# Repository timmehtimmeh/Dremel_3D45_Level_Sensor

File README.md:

# Dremel_3D45_Level_Sensor
KiCAD project, schematic, and gerbers of a Printed Circuit Board (PCB) replacement for The Auto_LevelBoard PCB for the Dremel 3D45 (and possibly the Dremel 3D40)
  **NOTE** Using this PCB will likely void any warranty provided with the printer.  An entire replacement leveling arm assembly can be [purchased directly from 3PITech](https://3pitech.com/products/3d45-leveling-sensor)

# Getting the Gerbers
If you only want to have the PCBs manufactured, navigate to the [releases page](https://github.com/timmehtimmeh/Dremel_3D45_Level_Sensor/releases/) and download the zip file of the gerbers

# Cloning the repo
This repository references the KiCAD symbol and footprint libraries stored in [Tims-KiCad-Library](https://github.com/timmehtimmeh/Tims-KiCad-Library) to properly clone this repo please type the following into a git command window:

```git clone --recurse-submodules https://github.com/timmehtimmeh/Dremel_3D45_Level_Sensor.git```

# Parts required

The following parts are required to replace the PCB

| Part | Qty | Link | Notes|
|------|-----|------|------|
| PCB | 1 | I had the gerbers successfully manufactured at [JLCPCB](https://jlcpcb.com/) as well as [OSHPark*](https://oshpark.com/shared_projects/k3kUrSLB) | * **NOTE:** The original Dremel PCB is 1mm thick.  OshPark only makes standard thickness 1.6 mm boards, but the thicker 1.6mm board worked fine in the printer. JLCPCB has options for 1mm thick boards |
| Switch | 1 | The OEM seems to be a [Panasonic ESE-31R15T](https://www.digikey.com/en/products/detail/panasonic-electronic-components/ESE-31R15T/3163183) | An alternate can be the [TE Connectivity JJJHRGG200NOPMRTR](https://www.digikey.com/en/products/detail/te-connectivity-alcoswitch-switches/JJJHRGG200NOPMRTR/9452492), but in testing the Panasonic part was less prone to getting stuck in the housing |
| Jumper Wire | 2  | [Wire](https://www.amazon.com/dp/B089CWGQKW) |  The OEM is 26 AWG stranded wire, 90 mm, 1 red, one black Outer Diameter (O.D) 1mm. I used the 1.2 mm O.D. 28 AWG silicone coated wire linked, and it still fits inside the cable routing cutouts on the level arm. |
| 2 Position JST-PH 2mm Connector | 1 | [JST Kit](https://www.amazon.com/dp/B0F485CN38) | I used the kit linked, however you can also buy pre-assembled wires  |

Additionally Soldering equipment (iron, solder), and either Silicone glue, or Hot Glue are needed to complete the job.

# Assembly Instructions

Tools Needed
1.  2mm Hex bit or Hex wrench (Allen key)
2.  T10 Torx (star) screwdriver
3.  T7 Torx (star) screwdriver
4.  Replacement PCB

Once you have gathered the necessary components, assembly is relatively straightforward.
1. Place the switch onto the PCB such that the alignment holes in the bottom of the switch mate with the holes in the PCB
2. Ensure that the switch is centered and square to the board
3. Solder on one of the four pads of the switch.
4. Check Alignment of the switch.  If it's moved heat up the one pad and move the switch until it's square with the board and then let the solder cool
5. Solder the remaining three pads of the switch
6. (Optional) Solder the two jumper pads such that the jumpers make contact. This connects the switch housing to one leg of the switch.  If using the TE Connectivity switch there is no metal housing and this step can be skipped.  If using the Panasonic switch then the circuit will work with or without the jumpers connected together.
7. Strip approximately 2mm of insulation off of one end of each of a black and red wire.
8. Crimp JST-PH connectors onto each of the wires
9. Push the crimped end into a two position JST-PH connector (the red/black orientation doesn't matter, but I kept mine the same as the original board)
10. Cut the wires such that they're both equal in length, and the same length as the OEM wire (approximately 90mm)
11. Strip 2-3mm of insulation off the cut end of the wire
12. Solder the red wire onto the PCB where the silkscreen indicates the red wire should go
13. Solder the black wire onto the PCB where the silkscreen indicates the black wire should go
14. Place the board on something that will allow you to put some silicone or hot glue onto the wires & board
15. Put a blob of glue such that it covers the two soldered ends of the wire and travels a bit up the wire to provide some strain relief.  Be sure to not allow too much glue to blob on the back side of the PCB
16. Once the glue is set, follow Steps 1, 2, and 5 from [these instructions](https://cdn.shopify.com/s/files/1/0552/1797/9558/files/3d45-3d40-leveling-arm-replacement.pdf)
17. Unscrew the PCB from the leveling arm assembly on your printer, taking care to not lose the screw or washer that holds the PCB in place
18. Carefully pull the wires out of the plastic wire guide on the leveling arm assembly, and remove the old PCB from the assembly
19. Thread the JST-PH connector from the new PCB through the appropriate area in the 3D printer head assembly and attach it to the printer, re-attach the servo motor wire if it was disconnected
20. Place the PCB into the sensor arm such that the plastic locating pin holds the PCB in place.
21. Using the T7 torx screwdriver, attach PCB using the screw & washer that was taken out in Step 17.
22. Reassemble the Extruder by following Step 6 in [these instructions](https://cdn.shopify.com/s/files/1/0552/1797/9558/files/3d45-3d40-leveling-arm-replacement.pdf)
23. If necessary, calibrate the level arm up/down position by navigating to TOOLS>SETTINGS>SERVICE TOOLS>LEVELING SWITCH and set the level (Step 7 in the linked instructions)
24. Calibrate the nozzle gap by following [these instructions](https://www.dremel.com/binaries/content/assets/dremel/uk/digilab/how-to-self-repair/3d45/3d45-nozzle-gap-calibration.pdf)

**Notes** - After a few uses I found that the replacment switch was not rebounding as quickly as it should.  To fix this i used a little bit of nonconductive spray lubricant on the tip of the switch and moved the switch in and out a few times after which the switch rebounded much more quickly.

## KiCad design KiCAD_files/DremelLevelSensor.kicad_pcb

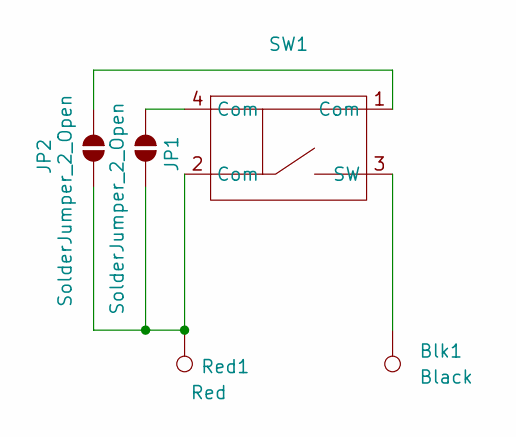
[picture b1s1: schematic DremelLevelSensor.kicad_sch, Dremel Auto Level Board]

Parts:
Blk1: Black; TestPoint_Pad_D1.5mm
JP1, JP2: SolderJumper_2_Open; SolderJumper-2_P1.3mm_Open_RoundedPad1.0x1.5mm
Red1: Red; TestPoint_Pad_D1.5mm
SW1: ESE31R11T

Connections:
GND: JP1.1 (A), JP2.1 (A), Red1.1, SW1.2 (Com)
unnamed: JP1.2 (B), SW1.4 (Com)
unnamed: JP2.2 (B), SW1.1 (Com)
unnamed: Blk1.1, SW1.3 (SW)

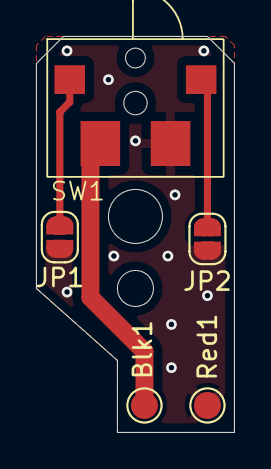
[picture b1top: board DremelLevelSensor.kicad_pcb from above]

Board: 2 copper layers, 11.0 x 22.0 mm, 5 parts (0 on the bottom side), 4 nets.

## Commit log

2026-02-08 Update README to include KiCAD project details
2026-02-08 Add KiCad files
2026-02-08 Add kicad gitignore file
2026-02-08 fix markdown table
2026-02-08 space between header and table
2026-02-08 Fix table
2026-02-08 fix links
2026-02-08 fix text in wire section
2026-02-08 Update OSHPark Link
2026-02-08 Add image, update README
2026-02-08 Update PCB and Schematic to remove unnecessary jumper that was added to try to get DKRed to work
2026-02-08 Move KiCAD Files folder, add pdf of schematic
2026-02-08 Add Footprint & Symbol library as git submodule. Reference the footprint & symbols as project specific libraries
2026-02-08 Update README with more instructions
